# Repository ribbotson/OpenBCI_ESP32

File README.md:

# OpenBCI_ESP32
Clone of OpenBCI Brain Computer Interface Hardware using ESP32 Processor

>OpenBCI Cyton is a well performing Open source hardware and software design for a Brain Computer Interface. It was designed and developed over the last 7 years and used in many experimants and applications.
>This clone is designed because some of the parts used in the Cyton hardware are now obsolete and difficult to source. Also it is hoped that a new design can offer higher throughput. 
The design will continue to use the TI ADS1299 Analog Front end so perfomance should be the same as Cyton. The option to have either 8 or 16 channels will be retained.

## Changes for ESP Version

**Replace existing PIC32MX processor with ESP32 processor with integral WiFi and Bluetooth**

>The ESP32 was chosen because it has integral WiFi and bluetooth and so replaces the obsolete RFD22301 bluetooth module and the WiFi board. The ESP32 is better supported under Arduino environment than PIC and RFD device. Raspberry Pi Zero W was considered as it has more processing power, but was excluded due to much higher power consumption so not suitable for battery operation.

**The design is split into two plugable modules**

>The base module supports the Processor, Micro SD Card, Accelerometer, and Power Supplies. One or two input modules are the stacked below to add 8 or 16 electrode inputs. The first base module will use a prebuilt ESP32 DEVkit C module to make firmware development easier. A later version could place as smaller ESP32 module directly on the base module.

**Boards only have components on one side**

>To simplify construction the new boards only have components mounted on one side of the board. Both boards are 2 layer PCB.

**Some components are to allow use of more common generic devices**

>Use of more common generic components should help with procurement especially if using outsourced PCB Assembly

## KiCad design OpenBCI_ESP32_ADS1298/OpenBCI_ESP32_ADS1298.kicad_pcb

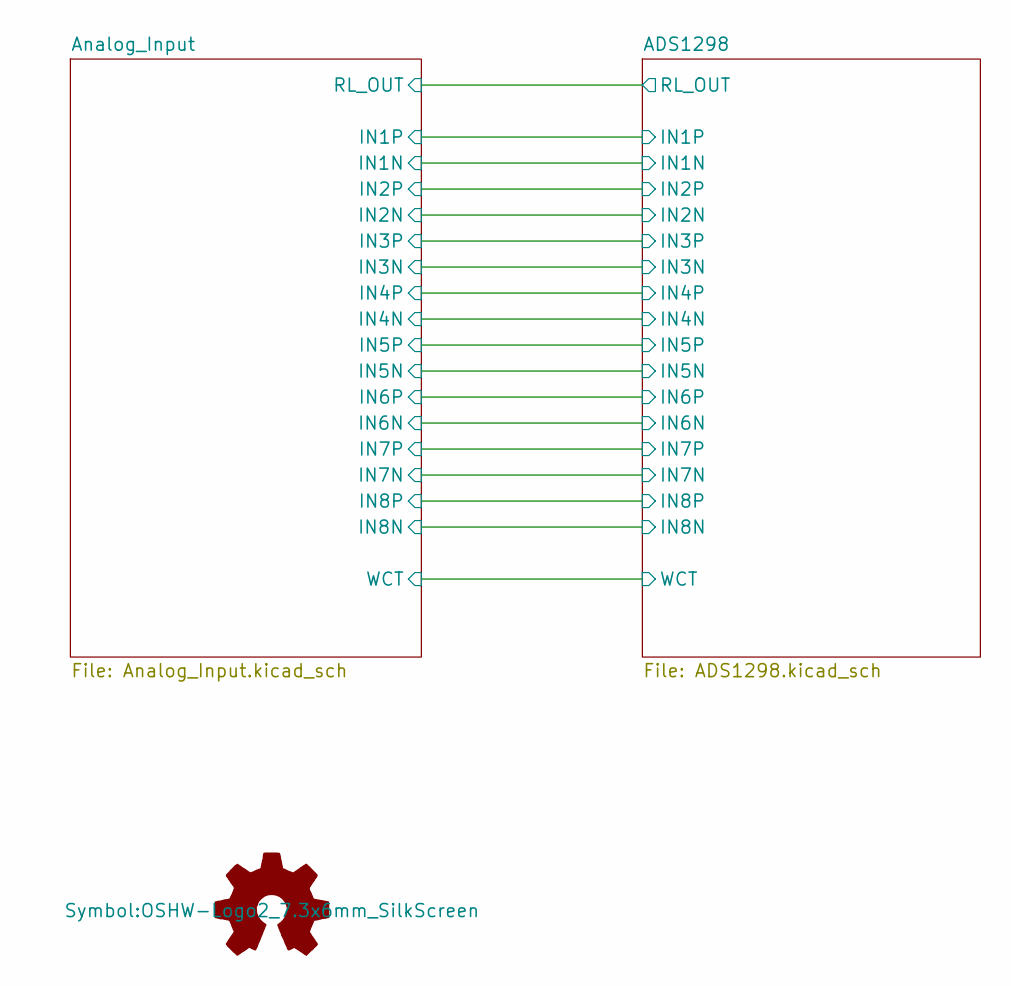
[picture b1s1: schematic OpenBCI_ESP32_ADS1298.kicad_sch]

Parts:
LOGO1: Logo_Open_Hardware_Small; OSHW-Logo2_7.3x6mm_SilkScreen

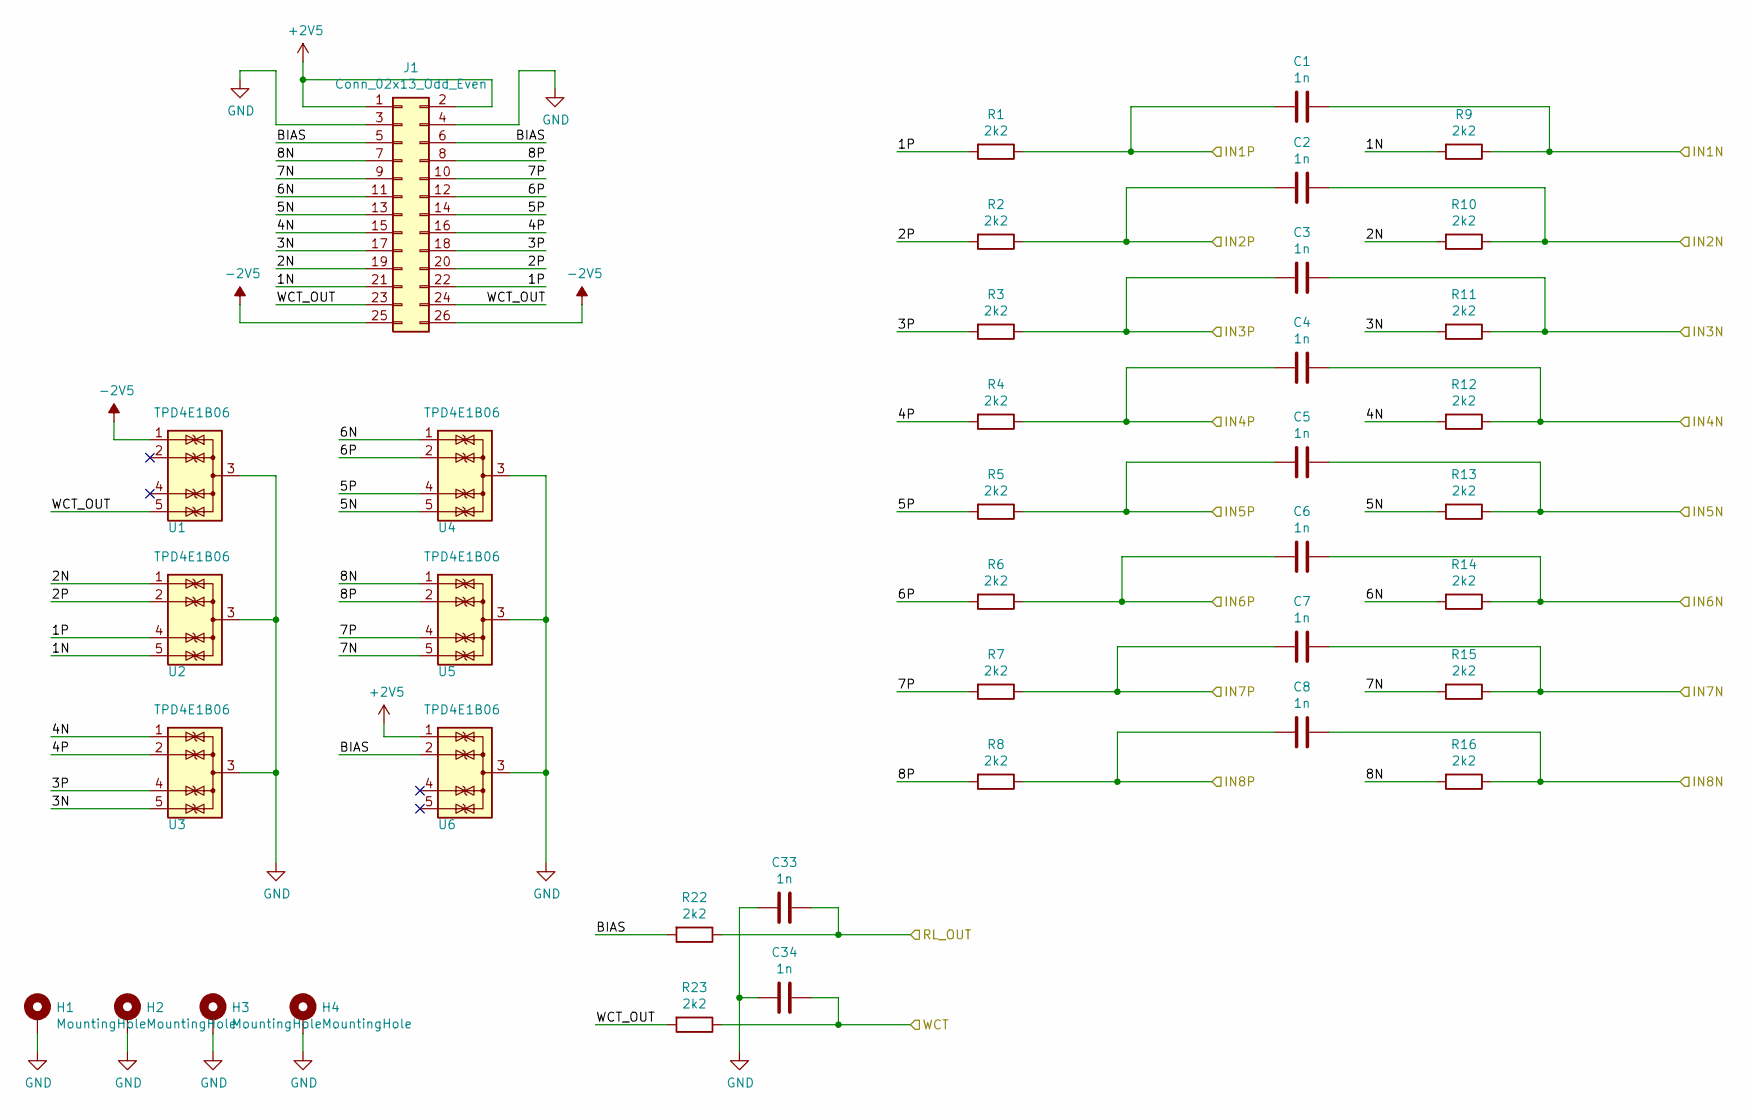
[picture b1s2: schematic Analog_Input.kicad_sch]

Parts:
C1, C2, C3, C4, C5, C6, C7, C8, C33, C34: 1n; C_0603_1608Metric
H1, H2, H3, H4: MountingHole; MountingHole_2.7mm_M2.5_DIN965_Pad_TopBottom
J1: Conn_02x13_Odd_Even; PinHeader_2x13_P2.54mm_OpenBCI
R1, R2, R3, R4, R5, R6, R7, R8, R9, R10, R11, R12, R13, R14, R15, R16, R22, R23: 2k2; R_0603_1608Metric
U1, U2, U3, U4, U5, U6: TPD4E1B06; SOT-363_SC-70-6

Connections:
+2V5: J1.1, J1.2, U6.1 (IO1); also elsewhere on the board
-2V5: J1.25, J1.26, U1.1 (IO1); also elsewhere on the board
/ADS1298/IN1N: C1.1, R9.1; also elsewhere on the board
/ADS1298/IN1P: C1.2, R1.1; also elsewhere on the board
/ADS1298/IN2N: C2.1, R10.1; also elsewhere on the board
/ADS1298/IN2P: C2.2, R2.1; also elsewhere on the board
/ADS1298/IN3N: C3.1, R11.1; also elsewhere on the board
/ADS1298/IN3P: C3.2, R3.1; also elsewhere on the board
/ADS1298/IN4N: C4.1, R12.1; also elsewhere on the board
/ADS1298/IN4P: C4.2, R4.1; also elsewhere on the board
/ADS1298/IN5N: C5.1, R13.1; also elsewhere on the board
/ADS1298/IN5P: C5.2, R5.1; also elsewhere on the board
/ADS1298/IN6N: C6.1, R14.1; also elsewhere on the board
/ADS1298/IN6P: C6.2, R6.1; also elsewhere on the board
/ADS1298/IN7N: C7.1, R15.1; also elsewhere on the board
/ADS1298/IN7P: C7.2, R7.1; also elsewhere on the board
/ADS1298/IN8N: C8.1, R16.1; also elsewhere on the board
/ADS1298/IN8P: C8.2, R8.1; also elsewhere on the board
/ADS1298/RL_OUT: C33.1, R22.1; also elsewhere on the board
/ADS1298/WCT: C34.1, R23.1; also elsewhere on the board
/Analog_Input/1N: J1.21, R9.2, U2.5 (IO4)
/Analog_Input/1P: J1.22, R1.2, U2.4 (IO3)
/Analog_Input/2N: J1.19, R10.2, U2.1 (IO1)
/Analog_Input/2P: J1.20, R2.2, U2.2 (IO2)
/Analog_Input/3N: J1.17, R11.2, U3.5 (IO4)
/Analog_Input/3P: J1.18, R3.2, U3.4 (IO3)
/Analog_Input/4N: J1.15, R12.2, U3.1 (IO1)
/Analog_Input/4P: J1.16, R4.2, U3.2 (IO2)
/Analog_Input/5N: J1.13, R13.2, U4.5 (IO4)
/Analog_Input/5P: J1.14, R5.2, U4.4 (IO3)
/Analog_Input/6N: J1.11, R14.2, U4.1 (IO1)
/Analog_Input/6P: J1.12, R6.2, U4.2 (IO2)
/Analog_Input/7N: J1.9, R15.2, U5.5 (IO4)
/Analog_Input/7P: J1.10, R7.2, U5.4 (IO3)
/Analog_Input/8N: J1.7, R16.2, U5.1 (IO1)
/Analog_Input/8P: J1.8, R8.2, U5.2 (IO2)
/Analog_Input/BIAS: J1.5, J1.6, R22.2, U6.2 (IO2)
/Analog_Input/WCT_OUT: J1.23, J1.24, R23.2, U1.5 (IO4)
GND: C33.2, C34.2, H1.1, H2.1, H3.1, H4.1, J1.3, J1.4, U1.3 (G), U2.3 (G), U3.3 (G), U4.3 (G), U5.3 (G), U6.3 (G); also elsewhere on the board

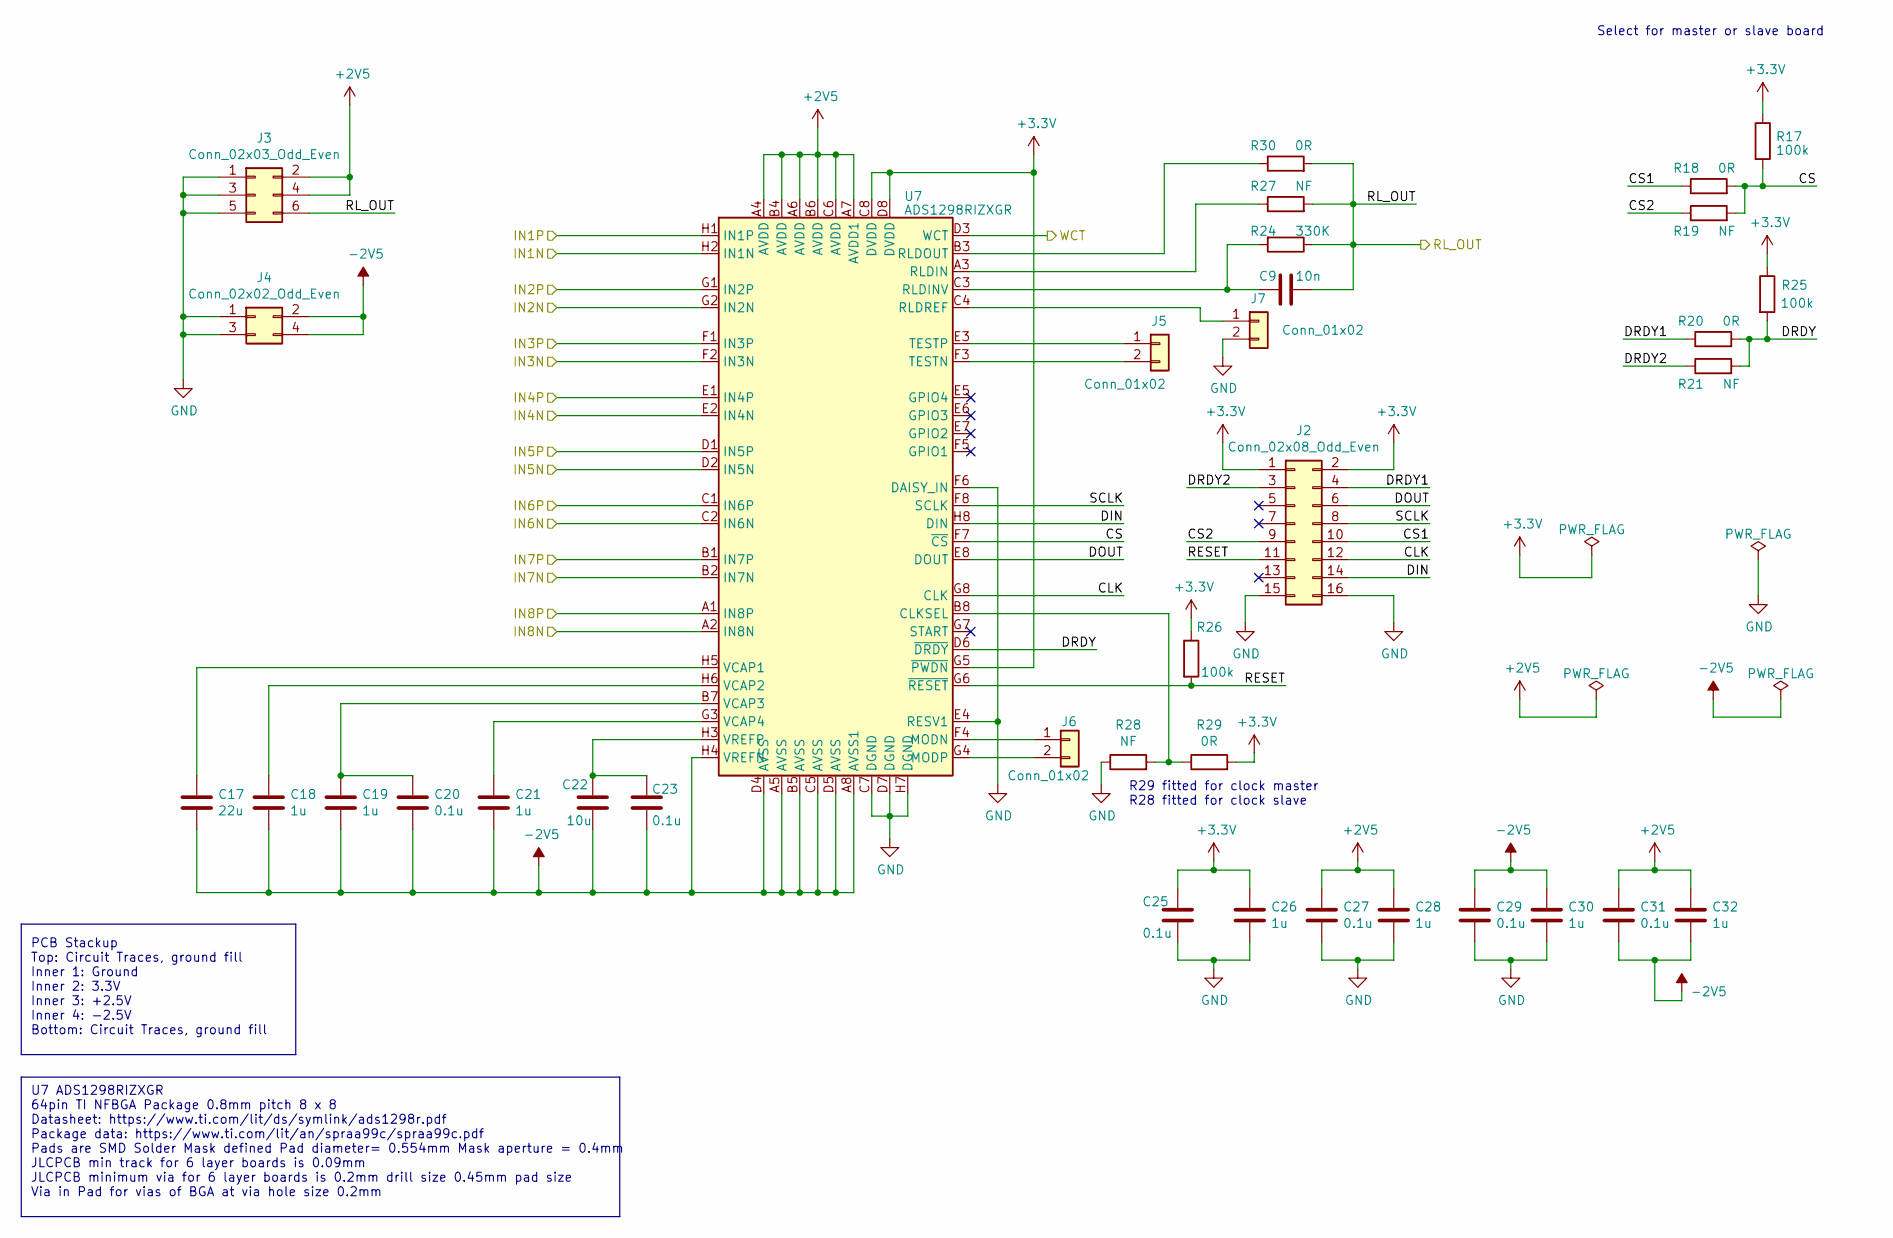
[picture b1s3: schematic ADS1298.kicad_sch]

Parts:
C9: 10n; C_0603_1608Metric
C17: 22u; C_0805_2012Metric
C18, C19, C21, C26, C28, C30, C32: 1u; C_0603_1608Metric
C20, C23, C25, C27, C29, C31: 0.1u; C_0603_1608Metric
C22: 10u; C_0805_2012Metric
J2: Conn_02x08_Odd_Even; PinSocket_2x08_P2.54mm_Vertical
J3: Conn_02x03_Odd_Even; PinSocket_2x03_P2.54mm_Vertical
J4: Conn_02x02_Odd_Even; PinSocket_2x02_P2.54mm_Vertical
J5, J6, J7: Conn_01x02; PinHeader_1x02_P2.00mm_Vertical
R17, R25, R26: 100k; R_0603_1608Metric
R18, R20, R29, R30: 0R; R_0603_1608Metric
R19, R21, R27, R28: NF; R_0603_1608Metric
R24: 330K; R_0603_1608Metric
U7: ADS1298RIZXGR; BGA-64_8x8_8.0x8.0mm

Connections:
+2V5: C27.1, C28.1, C31.1, C32.1, J3.2, J3.4, U7.A4 (AVDD), U7.A6 (AVDD), U7.A7 (AVDD1), U7.B4 (AVDD), U7.B6 (AVDD), U7.C6 (AVDD); also elsewhere on the board
+3.3V: C25.1, C26.1, J2.1, J2.2, R17.1, R25.1, R26.1, R29.2, U7.C8 (DVDD), U7.D8 (DVDD), U7.G5 (~PWDN)
-2V5: C17.2, C18.2, C19.2, C20.2, C21.2, C22.2, C23.2, C29.1, C30.1, C31.2, C32.2, J4.2, J4.4, U7.A5 (AVSS), U7.A8 (AVSS1), U7.B5 (AVSS), U7.C5 (AVSS), U7.D4 (AVSS), U7.D5 (AVSS), U7.H4 (VREFN); also elsewhere on the board
/ADS1298/CLK: J2.12, U7.G8 (CLK)
/ADS1298/CS: R17.2, R18.2, R19.2, U7.F7 (~CS)
/ADS1298/CS1: J2.10, R18.1
/ADS1298/CS2: J2.9, R19.1
/ADS1298/DIN: J2.14, U7.H8 (DIN)
/ADS1298/DOUT: J2.6, U7.E8 (DOUT)
/ADS1298/DRDY: R20.2, R21.2, R25.2, U7.D6 (~DRDY)
/ADS1298/DRDY1: J2.4, R20.1
/ADS1298/DRDY2: J2.3, R21.1
/ADS1298/IN1N: U7.H2 (IN1N); also elsewhere on the board
/ADS1298/IN1P: U7.H1 (IN1P); also elsewhere on the board
/ADS1298/IN2N: U7.G2 (IN2N); also elsewhere on the board
/ADS1298/IN2P: U7.G1 (IN2P); also elsewhere on the board
/ADS1298/IN3N: U7.F2 (IN3N); also elsewhere on the board
/ADS1298/IN3P: U7.F1 (IN3P); also elsewhere on the board
/ADS1298/IN4N: U7.E2 (IN4N); also elsewhere on the board
/ADS1298/IN4P: U7.E1 (IN4P); also elsewhere on the board
/ADS1298/IN5N: U7.D2 (IN5N); also elsewhere on the board
/ADS1298/IN5P: U7.D1 (IN5P); also elsewhere on the board
/ADS1298/IN6N: U7.C2 (IN6N); also elsewhere on the board
/ADS1298/IN6P: U7.C1 (IN6P); also elsewhere on the board
/ADS1298/IN7N: U7.B2 (IN7N); also elsewhere on the board
/ADS1298/IN7P: U7.B1 (IN7P); also elsewhere on the board
/ADS1298/IN8N: U7.A2 (IN8N); also elsewhere on the board
/ADS1298/IN8P: U7.A1 (IN8P); also elsewhere on the board
/ADS1298/RESET: J2.11, R26.2, U7.G6 (~RESET)
/ADS1298/RL_OUT: C9.2, J3.6, R24.1, R27.2, R30.2; also elsewhere on the board
/ADS1298/SCLK: J2.8, U7.F8 (SCLK)
/ADS1298/WCT: U7.D3 (WCT); also elsewhere on the board
GND: C25.2, C26.2, C27.2, C28.2, C29.2, C30.2, J2.15, J2.16, J3.1, J3.3, J3.5, J4.1, J4.3, J7.2, R28.1, U7.C7 (DGND), U7.D7 (DGND), U7.E4 (RESV1), U7.F6 (DAISY_IN), U7.H7 (DGND); also elsewhere on the board
unnamed: J5.1, U7.E3 (TESTP)
unnamed: J5.2, U7.F3 (TESTN)
unnamed: J6.1, U7.F4 (MODN)
unnamed: J6.2, U7.G4 (MODP)
unnamed: J7.1, U7.C4 (RLDREF)
unnamed: R28.2, R29.1, U7.B8 (CLKSEL)
unnamed: R27.1, U7.A3 (RLDIN)
unnamed: C9.1, R24.2, U7.C3 (RLDINV)
unnamed: R30.1, U7.B3 (RLDOUT)
unnamed: C17.1, U7.H5 (VCAP1)
unnamed: C18.1, U7.H6 (VCAP2)
unnamed: C19.1, C20.1, U7.B7 (VCAP3)
unnamed: C21.1, U7.G3 (VCAP4)
unnamed: C22.1, C23.1, U7.H3 (VREFP)

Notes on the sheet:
R29 fitted for clock master R28 fitted for clock slave
Select for master or slave board
U7 ADS1298RIZXGR 64pin TI NFBGA Package 0.8mm pitch 8 x 8 Datasheet: https://www.ti.com/lit/ds/symlink/ads1298r.pdf Package data: https://www.ti.com/lit/an/spraa99c/spraa99c.pdf Pads are SMD Solder Mask defined Pad diameter= 0.554mm Mask aperture = 0.4mm JLCPCB min track for 6 layer boards is 0.09m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
PCB Stackup Top: Circuit Traces, ground fill Inner 1: Ground Inner 2: 3.3V Inner 3: +2.5V Inner 4: -2.5V Bottom: Circuit Traces, ground fill

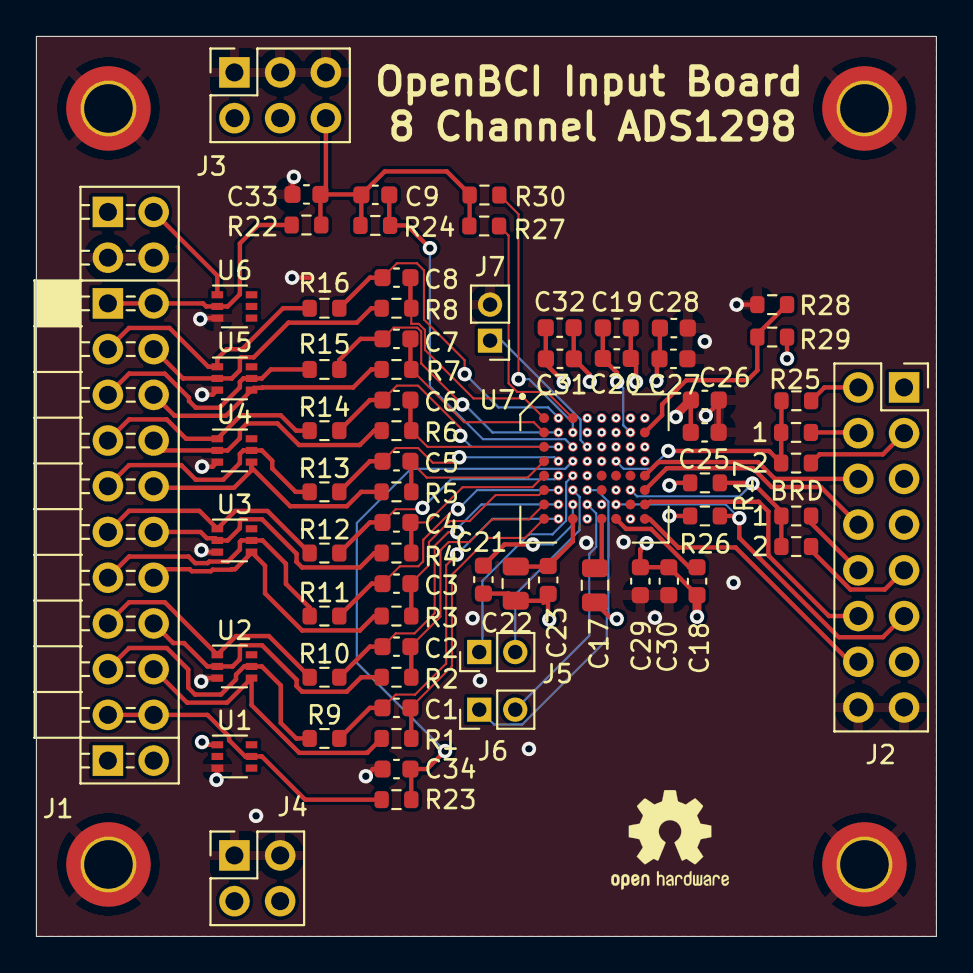
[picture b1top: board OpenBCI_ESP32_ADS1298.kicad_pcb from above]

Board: 6 copper layers, 50.0 x 50.0 mm, 75 parts (0 on the bottom side), 65 nets.

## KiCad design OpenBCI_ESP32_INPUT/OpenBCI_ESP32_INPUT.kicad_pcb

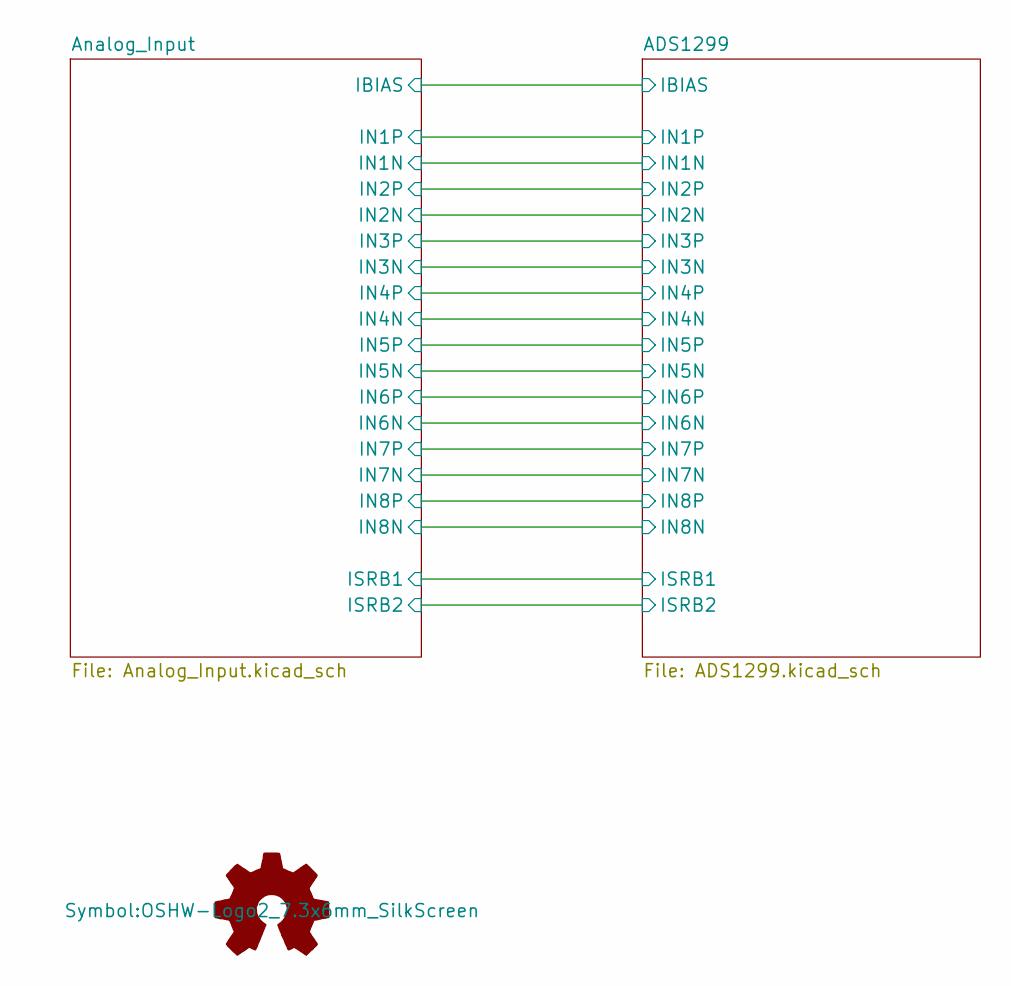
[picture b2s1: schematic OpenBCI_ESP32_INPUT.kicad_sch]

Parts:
LOGO1: Logo_Open_Hardware_Small; OSHW-Logo2_7.3x6mm_SilkScreen

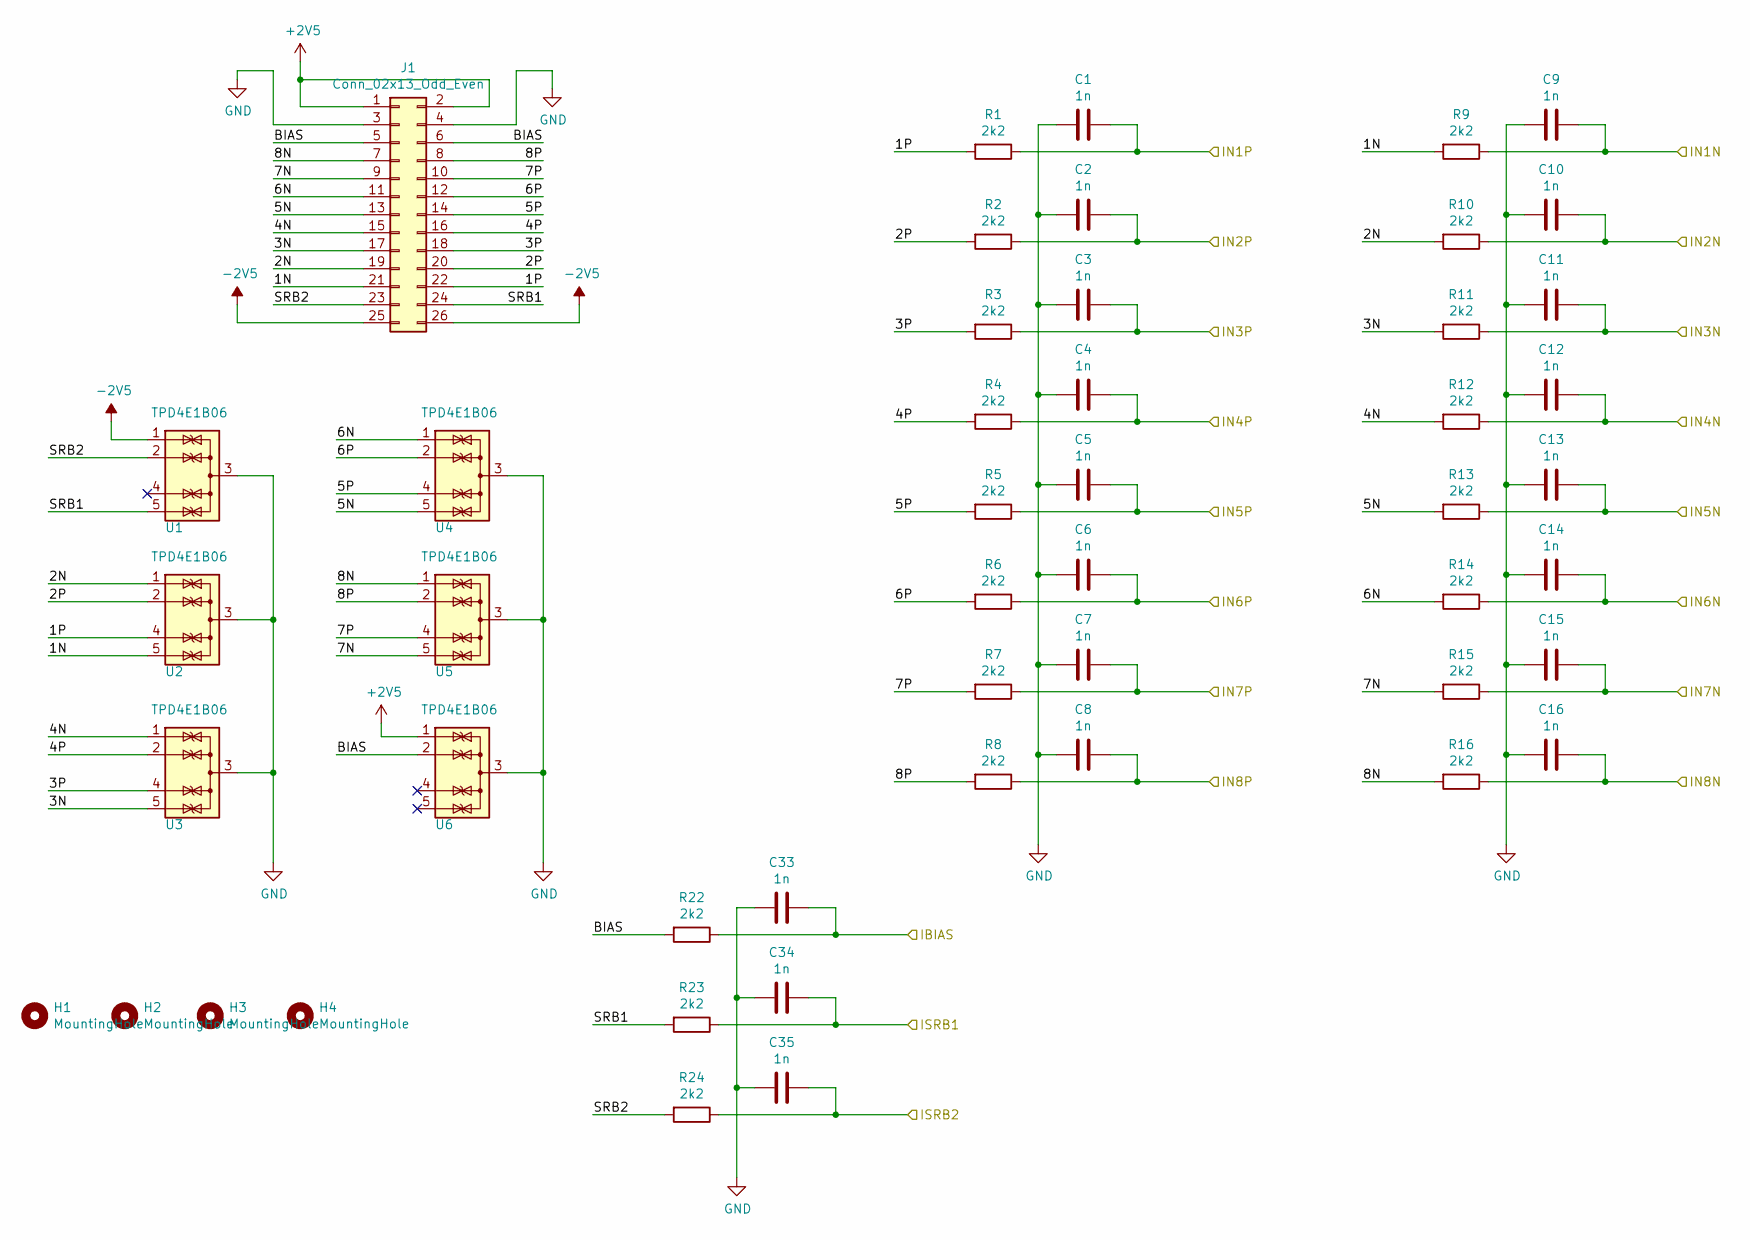
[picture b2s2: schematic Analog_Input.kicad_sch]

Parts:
C1, C2, C3, C4, C5, C6, C7, C8, C9, C10, C11, C12, C13, C14, C15, C16, C33, C34, C35: 1n; C_0603_1608Metric
H1, H2, H3, H4: MountingHole; MountingHole_2.7mm_M2.5
J1: Conn_02x13_Odd_Even; PinHeader_2x13_P2.54mm_OpenBCI
R1, R2, R3, R4, R5, R6, R7, R8, R9, R10, R11, R12, R13, R14, R15, R16, R22, R23, R24: 2k2; R_0603_1608Metric
U1, U2, U3, U4, U5, U6: TPD4E1B06; SOT-363_SC-70-6

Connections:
+2V5: J1.1, J1.2, U6.1 (IO1); also elsewhere on the board
-2V5: J1.25, J1.26, U1.1 (IO1); also elsewhere on the board
/ADS1299/IBIAS: C33.1, R22.1; also elsewhere on the board
/ADS1299/IN1N: C9.1, R9.1; also elsewhere on the board
/ADS1299/IN1P: C1.1, R1.1; also elsewhere on the board
/ADS1299/IN2N: C10.1, R10.1; also elsewhere on the board
/ADS1299/IN2P: C2.1, R2.1; also elsewhere on the board
/ADS1299/IN3N: C11.1, R11.1; also elsewhere on the board
/ADS1299/IN3P: C3.1, R3.1; also elsewhere on the board
/ADS1299/IN4N: C12.1, R12.1; also elsewhere on the board
/ADS1299/IN4P: C4.1, R4.1; also elsewhere on the board
/ADS1299/IN5N: C13.1, R13.1; also elsewhere on the board
/ADS1299/IN5P: C5.1, R5.1; also elsewhere on the board
/ADS1299/IN6N: C14.1, R14.1; also elsewhere on the board
/ADS1299/IN6P: C6.1, R6.1; also elsewhere on the board
/ADS1299/IN7N: C15.1, R15.1; also elsewhere on the board
/ADS1299/IN7P: C7.1, R7.1; also elsewhere on the board
/ADS1299/IN8N: C16.1, R16.1; also elsewhere on the board
/ADS1299/IN8P: C8.1, R8.1; also elsewhere on the board
/ADS1299/ISRB1: C34.1, R23.1; also elsewhere on the board
/ADS1299/ISRB2: C35.1, R24.1; also elsewhere on the board
/Analog_Input/1N: J1.21, R9.2, U2.5 (IO4)
/Analog_Input/1P: J1.22, R1.2, U2.4 (IO3)
/Analog_Input/2N: J1.19, R10.2, U2.1 (IO1)
/Analog_Input/2P: J1.20, R2.2, U2.2 (IO2)
/Analog_Input/3N: J1.17, R11.2, U3.5 (IO4)
/Analog_Input/3P: J1.18, R3.2, U3.4 (IO3)
/Analog_Input/4N: J1.15, R12.2, U3.1 (IO1)
/Analog_Input/4P: J1.16, R4.2, U3.2 (IO2)
/Analog_Input/5N: J1.13, R13.2, U4.5 (IO4)
/Analog_Input/5P: J1.14, R5.2, U4.4 (IO3)
/Analog_Input/6N: J1.11, R14.2, U4.1 (IO1)
/Analog_Input/6P: J1.12, R6.2, U4.2 (IO2)
/Analog_Input/7N: J1.9, R15.2, U5.5 (IO4)
/Analog_Input/7P: J1.10, R7.2, U5.4 (IO3)
/Analog_Input/8N: J1.7, R16.2, U5.1 (IO1)
/Analog_Input/8P: J1.8, R8.2, U5.2 (IO2)
/Analog_Input/BIAS: J1.5, J1.6, R22.2, U6.2 (IO2)
/Analog_Input/SRB1: J1.24, R23.2, U1.5 (IO4)
/Analog_Input/SRB2: J1.23, R24.2, U1.2 (IO2)
GND: C1.2, C2.2, C3.2, C4.2, C5.2, C6.2, C7.2, C8.2, C9.2, C10.2, C11.2, C12.2, C13.2, C14.2, C15.2, C16.2, C33.2, C34.2, C35.2, J1.3, J1.4, U1.3 (G), U2.3 (G), U3.3 (G), U4.3 (G), U5.3 (G), U6.3 (G); also elsewhere on the board

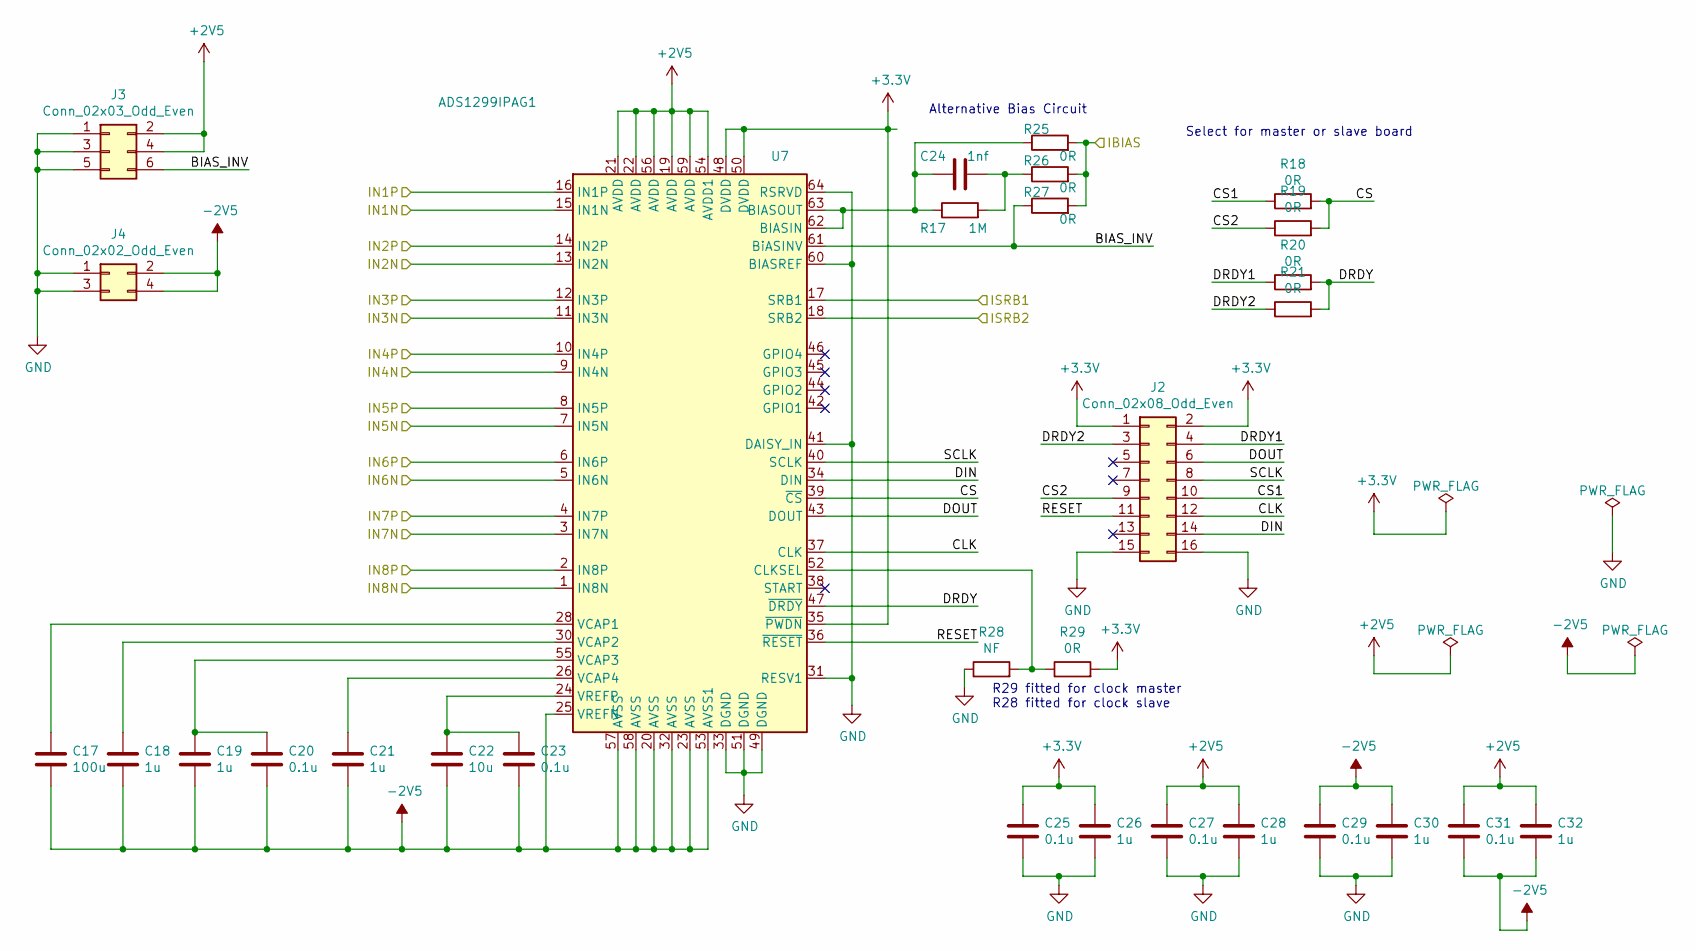
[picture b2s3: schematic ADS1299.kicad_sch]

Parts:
C17: 100u; C_1210_3225Metric
C18, C19, C21, C26, C28, C30, C32: 1u; C_0603_1608Metric
C20, C23, C25, C27, C29, C31: 0.1u; C_0603_1608Metric
C22: 10u; C_0805_2012Metric
C24: 1nf; C_0603_1608Metric
J2: Conn_02x08_Odd_Even; PinSocket_2x08_P2.54mm_Vertical
J3: Conn_02x03_Odd_Even; PinSocket_2x03_P2.54mm_Vertical
J4: Conn_02x02_Odd_Even; PinSocket_2x02_P2.54mm_Vertical
R17: 1M; R_0603_1608Metric
R18, R19, R20, R21, R25, R26, R27, R29: 0R; R_0603_1608Metric
R28: NF; R_0603_1608Metric
U7: ADS1299IPAG1; TQFP-64_10x10mm_P0.5mm

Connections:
+2V5: C27.1, C28.1, C31.1, C32.1, J3.2, J3.4, U7.19 (AVDD), U7.21 (AVDD), U7.22 (AVDD), U7.54 (AVDD1), U7.56 (AVDD), U7.59 (AVDD); also elsewhere on the board
+3.3V: C25.1, C26.1, J2.1, J2.2, R29.2, U7.35 (~PWDN), U7.48 (DVDD), U7.50 (DVDD)
-2V5: C17.2, C18.2, C19.2, C20.2, C21.2, C22.2, C23.2, C29.1, C30.1, C31.2, C32.2, J4.2, J4.4, U7.20 (AVSS), U7.23 (AVSS), U7.25 (VREFN), U7.32 (AVSS), U7.53 (AVSS1), U7.57 (AVSS), U7.58 (AVSS); also elsewhere on the board
/ADS1299/BIAS_INV: J3.6, R27.1, U7.61 (BiASINV)
/ADS1299/CLK: J2.12, U7.37 (CLK)
/ADS1299/CS: R18.2, R19.2, U7.39 (~CS)
/ADS1299/CS1: J2.10, R18.1
/ADS1299/CS2: J2.9, R19.1
/ADS1299/DIN: J2.14, U7.34 (DIN)
/ADS1299/DOUT: J2.6, U7.43 (DOUT)
/ADS1299/DRDY: R20.2, R21.2, U7.47 (~DRDY)
/ADS1299/DRDY1: J2.4, R20.1
/ADS1299/DRDY2: J2.3, R21.1
/ADS1299/IBIAS: R25.2, R26.2, R27.2; also elsewhere on the board
/ADS1299/IN1N: U7.15 (IN1N); also elsewhere on the board
/ADS1299/IN1P: U7.16 (IN1P); also elsewhere on the board
/ADS1299/IN2N: U7.13 (IN2N); also elsewhere on the board
/ADS1299/IN2P: U7.14 (IN2P); also elsewhere on the board
/ADS1299/IN3N: U7.11 (IN3N); also elsewhere on the board
/ADS1299/IN3P: U7.12 (IN3P); also elsewhere on the board
/ADS1299/IN4N: U7.9 (IN4N); also elsewhere on the board
/ADS1299/IN4P: U7.10 (IN4P); also elsewhere on the board
/ADS1299/IN5N: U7.7 (IN5N); also elsewhere on the board
/ADS1299/IN5P: U7.8 (IN5P); also elsewhere on the board
/ADS1299/IN6N: U7.5 (IN6N); also elsewhere on the board
/ADS1299/IN6P: U7.6 (IN6P); also elsewhere on the board
/ADS1299/IN7N: U7.3 (IN7N); also elsewhere on the board
/ADS1299/IN7P: U7.4 (IN7P); also elsewhere on the board
/ADS1299/IN8N: U7.1 (IN8N); also elsewhere on the board
/ADS1299/IN8P: U7.2 (IN8P); also elsewhere on the board
/ADS1299/ISRB1: U7.17 (SRB1); also elsewhere on the board
/ADS1299/ISRB2: U7.18 (SRB2); also elsewhere on the board
/ADS1299/RESET: J2.11, U7.36 (~RESET)
/ADS1299/SCLK: J2.8, U7.40 (SCLK)
GND: C25.2, C26.2, C27.2, C28.2, C29.2, C30.2, J2.15, J2.16, J3.1, J3.3, J3.5, J4.1, J4.3, R28.1, U7.31 (RESV1), U7.33 (DGND), U7.41 (DAISY_IN), U7.49 (DGND), U7.51 (DGND), U7.60 (BIASREF), U7.64 (RSRVD); also elsewhere on the board
unnamed: C24.2, R17.2, R26.1
unnamed: C24.1, R17.1, R25.1, U7.62 (BIASIN), U7.63 (BIASOUT)
unnamed: R28.2, R29.1, U7.52 (CLKSEL)
unnamed: C17.1, U7.28 (VCAP1)
unnamed: C18.1, U7.30 (VCAP2)
unnamed: C19.1, C20.1, U7.55 (VCAP3)
unnamed: C21.1, U7.26 (VCAP4)
unnamed: C22.1, C23.1, U7.24 (VREFP)

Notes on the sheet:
R29 fitted for clock master R28 fitted for clock slave
Select for master or slave board
Alternative Bias Circuit

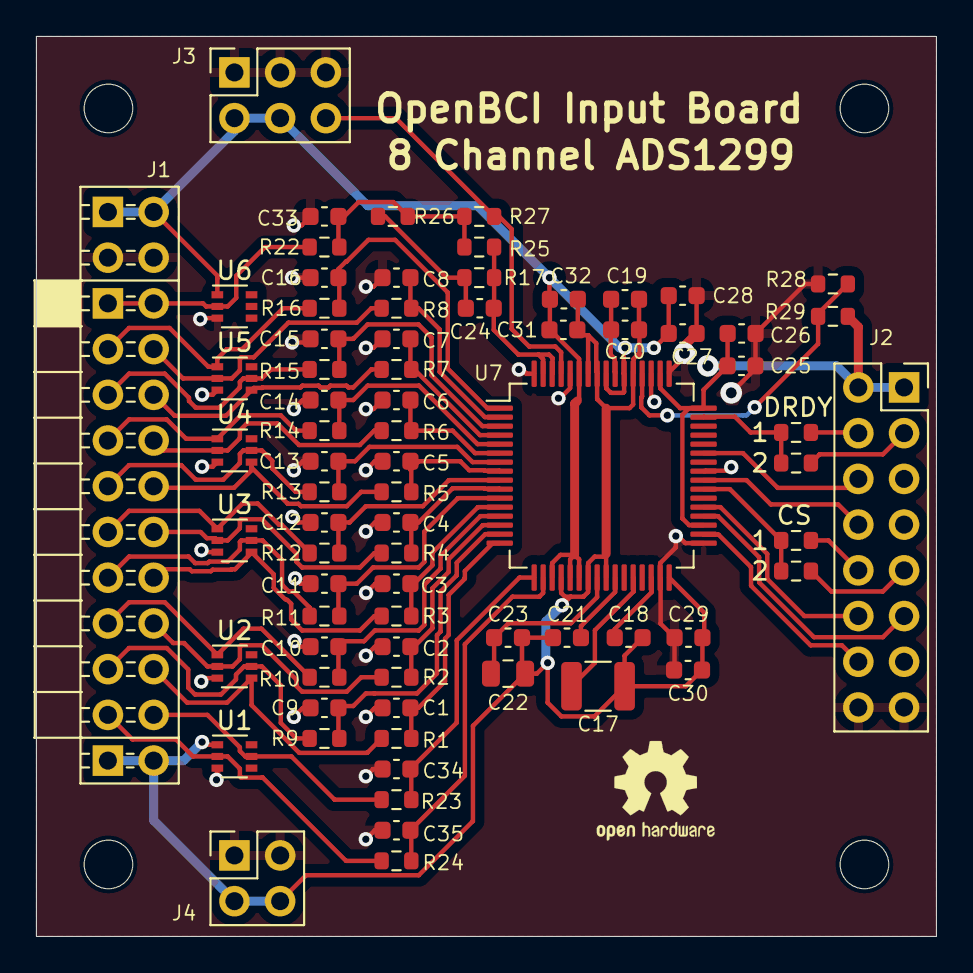
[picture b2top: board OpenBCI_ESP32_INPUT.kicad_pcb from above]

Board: 2 copper layers, 50.0 x 50.0 mm, 80 parts (0 on the bottom side), 62 nets.

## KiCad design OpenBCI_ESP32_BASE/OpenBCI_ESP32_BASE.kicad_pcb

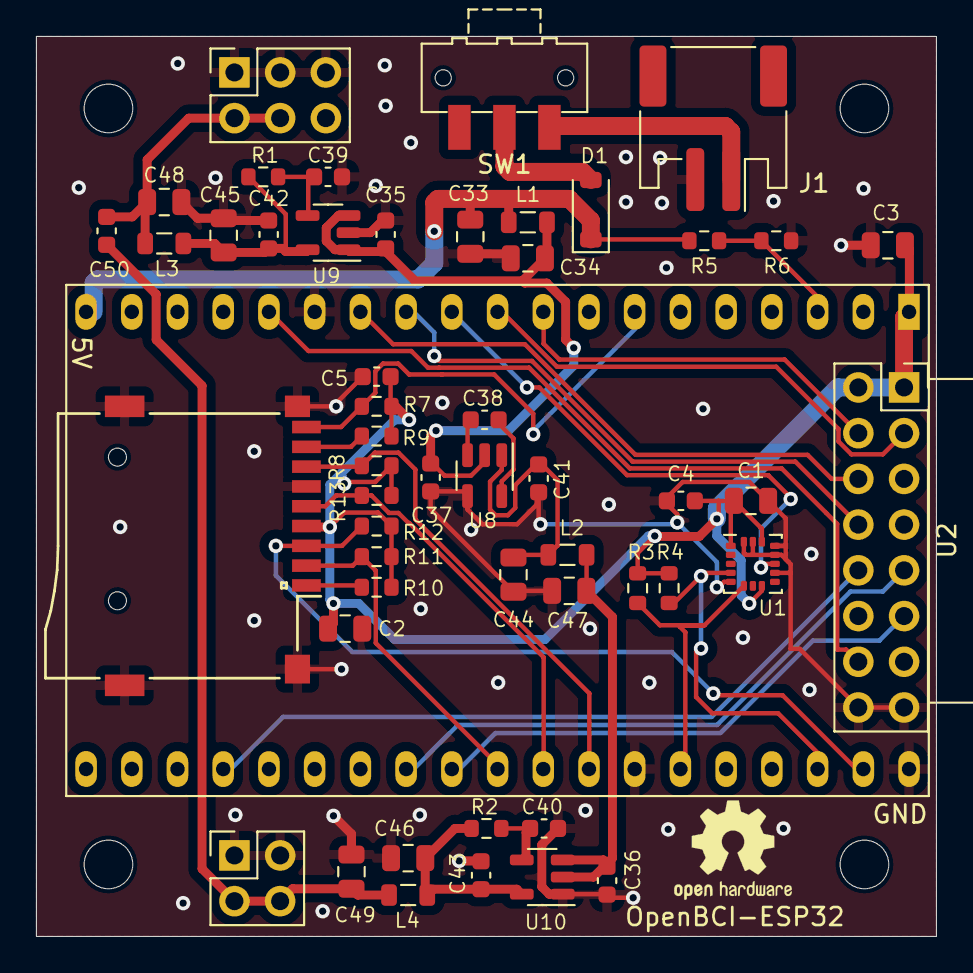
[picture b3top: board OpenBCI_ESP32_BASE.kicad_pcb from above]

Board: 2 copper layers, 50.0 x 50.0 mm, 57 parts (0 on the bottom side), 33 nets.

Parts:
C1, C2, C3, C33, C34, C44, C45, C46, C47, C48, C49: 10u; C_0805_2012Metric
C4, C5, C50: 0.1u; C_0603_1608Metric
C35, C37, C38, C39, C41: 1u; C_0603_1608Metric
C36, C42, C43: 2.2u; C_0603_1608Metric
C40: 10n; C_0603_1608Metric
D1: D_Schottky; D_SOD-123
H1, H2, H3, H4: MountingHole; MountingHole_2.7mm_M2.5
J1: Conn_01x02; JST_PH_S2B-PH-SM4-TB_1x02-1MP_P2.00mm_Horizontal
J2: Conn_02x03_Odd_Even; PinHeaderReverse_2x03_P2.54mm_OpenBCI
J3: Conn_02x02_Odd_Even; PinHeaderReverse_2x02_P2.54mml_OpenBCI
J4: Conn_02x08_Odd_Even; PinHeaderReverse_2x08_P2.54mm_OpenBCI
L1, L2, L3, L4: 3.3u; L_0805_2012Metric
LOGO1: Logo_Open_Hardware_Small; OSHW-Logo2_7.3x6mm_SilkScreen
R1, R2: NF; R_0603_1608Metric
R3, R4: 4k7; R_0603_1608Metric
R5: 220k; R_0603_1608Metric
R6: 120k; R_0603_1608Metric
R7, R8, R9, R10, R11, R12, R13: 10k; R_0603_1608Metric
SW1: SW_SPDT; SW_SPDT_CK-JS102011SAQN
U1: LIS3DH; LGA-16_3x3mm_P0.5mm_LayoutBorder3x5y
U2: ESP32-DevKitC
U8: TPS60403; SOT-23-5
U9: TPS73225; SOT-23-5
U10: TPS72325; SOT-23-5
XS1: SD_ebay-uSD-push_push_SMD; Conn_uSDcard

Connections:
+2V5: C48.1, C50.1, J2.2, J2.4, L3.2
+3.3V: C1.1, C2.1, C3.1, C4.1, C5.1, J4.1, J4.2, R3.1, R4.1, R7.1, R8.1, R9.1, R10.1, R11.1, R12.1, R13.1, U1.1 (VDD_IO), U1.8 (CS), U1.14 (VDD), U2.1 (3V3), XS1.4 (Vdd)
+5V: C33.1, D1.1 (K), L1.1, R5.1, U2.19 (5V)
-2V5: C49.1, C50.2, J3.2, J3.4, L4.2
-5V: C36.1, C47.1, L2.2, U10.2 (Vin), U10.3 (EN)
/OpenBCI_ESP_DEVKIT/ADSCLK: J4.8, U2.12 (MTMS/GPIO14/ADC2_CH6)
/OpenBCI_ESP_DEVKIT/ADSCS1: J4.10, U2.23 (*MTDO/GPIO15/ADC2_CH3)
/OpenBCI_ESP_DEVKIT/ADSCS2: J4.9, U2.27 (GPIO16)
/OpenBCI_ESP_DEVKIT/ADSDRDY1: J4.4, U2.9 (DAC_1/ADC2_CH8/GPIO25)
/OpenBCI_ESP_DEVKIT/ADSDRDY2: J4.3, U2.10 (DAC_2/ADC2_CH9/GPIO26)
/OpenBCI_ESP_DEVKIT/ADSMISO: J4.6, U2.13 (*MTDI/GPIO12/ADC2_CH5)
/OpenBCI_ESP_DEVKIT/ADSMOSI: J4.14, U2.15 (MTCK/GPIO13/ADC2_CH4)
/OpenBCI_ESP_DEVKIT/ADSRST: J4.11, U2.28 (GPIO17)
/OpenBCI_ESP_DEVKIT/INT1: U1.11 (INT1), U2.11 (ADC2_CH7/GPIO27)
/OpenBCI_ESP_DEVKIT/SCL: R4.2, U1.4 (SCL/SPC), U2.36 (GPIO22)
/OpenBCI_ESP_DEVKIT/SDA: R3.2, U1.6 (SDA/SDI/SDO), U2.33 (GPIO21)
/OpenBCI_ESP_DEVKIT/SDCD: R7.2, U2.7 (32K_XP/GPIO32/ADC1_CH4), XS1.9 (CD)
/OpenBCI_ESP_DEVKIT/SDCLK: R13.2, U2.30 (GPIO18), XS1.5 (CLK)
/OpenBCI_ESP_DEVKIT/SDCS: R11.2, U2.29 (*GPIO5), XS1.2 (CS/DAT3)
/OpenBCI_ESP_DEVKIT/SDMISO: R8.2, U2.31 (GPIO19), XS1.7 (DO/DAT0)
/OpenBCI_ESP_DEVKIT/SDMOSI: R12.2, U2.37 (GPIO23), XS1.3 (DI/CMD)
GND: C1.2, C2.2, C3.2, C4.2, C5.2, C33.2, C34.2, C35.2, C36.2, C37.2, C39.2, C40.2, C41.2, C42.2, C43.2, C44.2, C45.2, C46.2, C47.2, C48.2, C49.2, J1.2, J2.1, J2.3, J2.5, J3.1, J3.3, J4.15, J4.16, R6.2, U1.5 (GND), U1.10 (GND), U1.12 (GND), U1.13 (ADC3), U1.15 (ADC2), U1.16 (ADC1), U2.14 (GND), U2.32 (GND), U2.38 (GND), U8.4 (Gnd), U9.2 (Gnd), U10.1 (Gnd), XS1.6 (GND)
unnamed: D1.2 (A), SW1.2 (B)
unnamed: J1.1, SW1.1 (A)
unnamed: R5.2, R6.1, U2.3 (SENSOR_VP/GPIO36/ADC1_CH0)
unnamed: C38.1, U8.3 (Cfly1)
unnamed: C38.2, U8.5 (Cfly2)
unnamed: C34.1, C35.1, C37.1, L1.2, U8.2 (Vin), U9.1 (Vin), U9.3 (EN)
unnamed: C41.1, C44.1, L2.1, U8.1 (Vout)
unnamed: C39.1, R1.2, U9.4 (NR)
unnamed: C42.1, C45.1, L3.1, R1.1, U9.5 (Vout)
unnamed: C40.1, R2.2, U10.4 (NR)
unnamed: C43.1, C46.1, L4.1, R2.1, U10.5 (Vout)
